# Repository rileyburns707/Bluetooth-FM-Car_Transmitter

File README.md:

# Bluetooth-FM-Car_Transmitter
This is every step I took to create a Bluetooth FM car transmitter so I could play music in my car. I started from nothing and worked through basic ideas of how it would work, the parts I would need, breadboarding it, and soldering it.

Overview:
Have a PCB that connects the BM20 chip and NS73M chip. Designed that PCB on Eagle.
Then connect M5StickC+ to PCB and program M5 using Arduino code

I will explain briefly what is needed for this project:

List of important things
- NS73M - FM transmitter
- BM20 - Bluetooth chip
- M5StickC+
- Cigarette lighter with USB-C
- PCB for NS73M for breadboard. Found one on OSH Park 
- PCB for BM20 for breadboard. Found one on OSH Park
- PCB for Bluetooth FM Transmitter. I created the PCB for this using Eagle. Everything for that PCB is in the "Eagle" file
- Arduino code. Code for the M5StickC+. Everything for that is in the "Arduino code" file
- Capacitor "EEE-FK1A560SR" from Digi-key
- Crystal "R26-32.768-12.5" from Digi-key
- Switch mode DC:DC converter "OKI-78SR-3.3/1.5-W36H-C" from Digi-key

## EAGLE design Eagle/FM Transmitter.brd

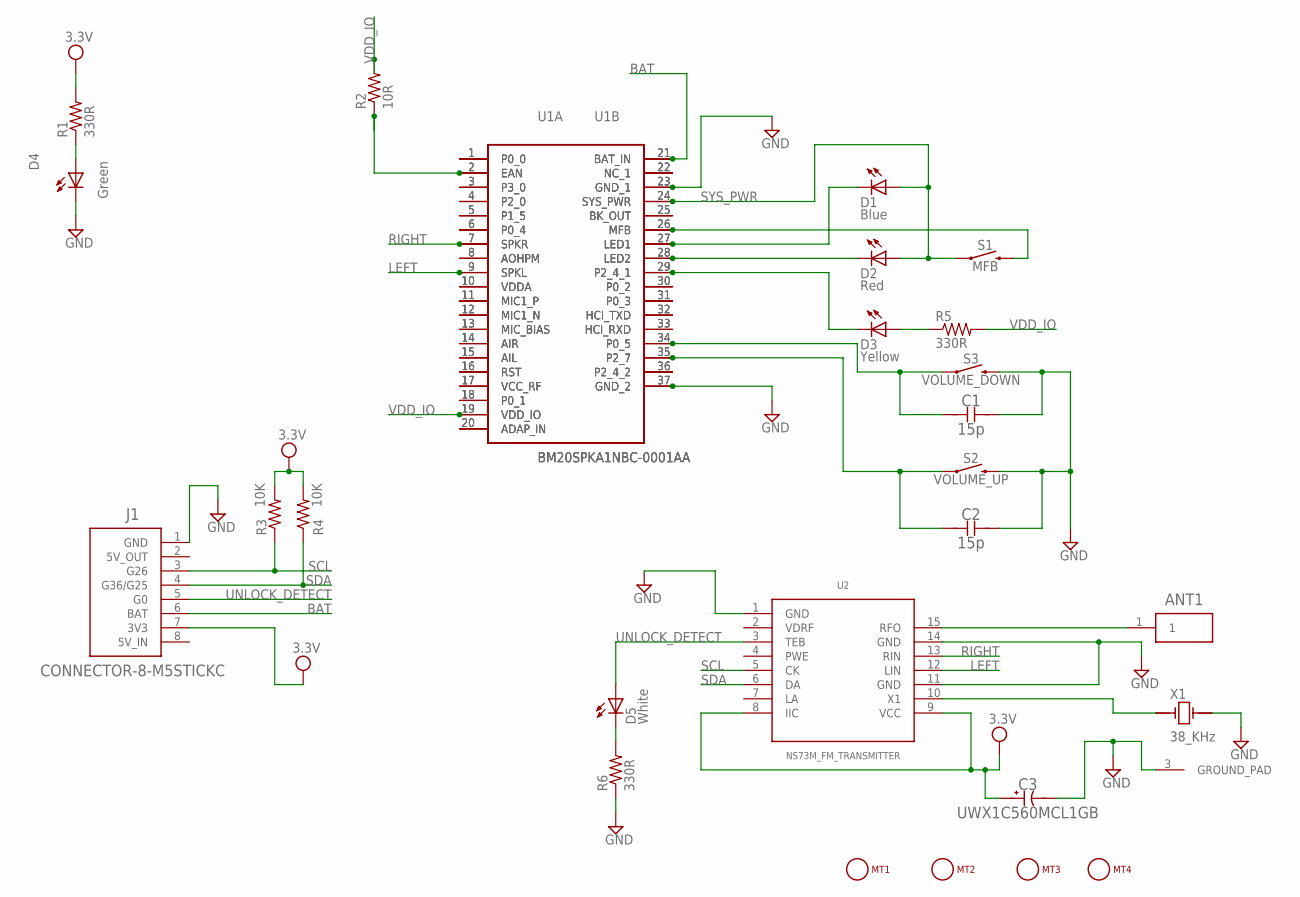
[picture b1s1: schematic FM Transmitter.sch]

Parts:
ANT1: CONNECTOR-1; ESQ-101-XX-X-S
C1, C2: 15p; CAPC2012X140N
C3: UWX1C560MCL1GB; PCAP_6.3X5.4-ELECT-M
D1: Blue; LED5MM
D2: Red; LED5MM
D3: Yellow; LED5MM
D4: Green; LED5MM
D5: White; LED5MM
J1: CONNECTOR-8-M5STICKC; ESQ-108-XX-X-S
MT1, MT2, MT3, MT4: MOUNTING_HOLE-125_250_ROUND; MT_125_250
R1, R5, R6: 330R; R0805
R2: 10R; R0805
R3, R4: 10K; R0805
S1: MFB; TACTILE_SWITCH_PTH_6.0MM
S2: VOLUME_UP; TACTILE_SWITCH_PTH_6.0MM
S3: VOLUME_DOWN; TACTILE_SWITCH_PTH_6.0MM
U1A, U1B: BM20SPKA1NBC-0001AA; BM20SPKA1NBC0001AA
U2: NS73M_FM_TRANSMITTER; NS73M
X1: 38_KHz; XTAL-WITH-GROUND-PAD

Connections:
3.3V: C3.1, J1.7 (3V3), R1.2, R3.2, R4.2, U2.8 (IIC), U2.9 (VCC)
BAT: J1.6 (BAT), U1A.21 (BAT_IN), U1B.21 (BAT_IN)
GND: C1.2, C2.2, C3.2, D4.K (C), J1.1 (GND), R6.1, S2.3 (2), S3.3 (2), U1A.23 (GND_1), U1A.37 (GND_2), U1B.23 (GND_1), U1B.37 (GND_2), U2.1 (GND), U2.11 (GND), U2.14 (GND), X1.2, X1.3 (GROUND_PAD)
LEFT: U1A.9 (SPKL), U1B.9 (SPKL), U2.12 (LIN)
unnamed: ANT1.1, U2.15 (RFO)
unnamed: D4.A, R1.1
unnamed: R2.1, U1A.2 (EAN), U1B.2 (EAN)
unnamed: D3.K (C), U1A.29 (P2_4_1), U1B.29 (P2_4_1)
unnamed: D2.K (C), U1A.28 (LED2), U1B.28 (LED2)
unnamed: D1.K (C), U1A.27 (LED1), U1B.27 (LED1)
unnamed: D3.A, R5.1
unnamed: D5.K (C), R6.2
unnamed: S1.3 (2), U1A.26 (MFB), U1B.26 (MFB)
unnamed: U2.10 (X1), X1.1
unnamed: C2.1, S2.1, U1A.35 (P2_7), U1B.35 (P2_7)
unnamed: C1.1, S3.1, U1A.34 (P0_5), U1B.34 (P0_5)
unnamed: U1A.1 (P0_0), U1B.1 (P0_0)
unnamed: U1A.3 (P3_0), U1B.3 (P3_0)
unnamed: U1A.4 (P2_0), U1B.4 (P2_0)
unnamed: U1A.5 (P1_5), U1B.5 (P1_5)
unnamed: U1A.6 (P0_4), U1B.6 (P0_4)
unnamed: U1A.8 (AOHPM), U1B.8 (AOHPM)
unnamed: U1A.10 (VDDA), U1B.10 (VDDA)
unnamed: U1A.11 (MIC1_P), U1B.11 (MIC1_P)
unnamed: U1A.12 (MIC1_N), U1B.12 (MIC1_N)
unnamed: U1A.13 (MIC_BIAS), U1B.13 (MIC_BIAS)
unnamed: U1A.14 (AIR), U1B.14 (AIR)
unnamed: U1A.15 (AIL), U1B.15 (AIL)
unnamed: U1A.16 (RST), U1B.16 (RST)
unnamed: U1A.17 (VCC_RF), U1B.17 (VCC_RF)
unnamed: U1A.18 (P0_1), U1B.18 (P0_1)
unnamed: U1A.20 (ADAP_IN), U1B.20 (ADAP_IN)
unnamed: U1A.22 (NC_1), U1B.22 (NC_1)
unnamed: U1A.25 (BK_OUT), U1B.25 (BK_OUT)
unnamed: U1A.30 (P0_2), U1B.30 (P0_2)
unnamed: U1A.31 (P0_3), U1B.31 (P0_3)
unnamed: U1A.32 (HCI_TXD), U1B.32 (HCI_TXD)
unnamed: U1A.33 (HCI_RXD), U1B.33 (HCI_RXD)
unnamed: U1A.36 (P2_4_2), U1B.36 (P2_4_2)
RIGHT: U1A.7 (SPKR), U1B.7 (SPKR), U2.13 (RIN)
SCL: J1.3 (G26), R3.1, U2.5 (CK)
SDA: J1.4 (G36/G25), R4.1, U2.6 (DA)
SYS_PWR: D1.A, D2.A, S1.1, U1A.24 (SYS_PWR), U1B.24 (SYS_PWR)
UNLOCK_DETECT: D5.A, J1.5 (G0), U2.3 (TEB)
VDD_IO: R2.2, R5.2, U1A.19 (VDD_IO), U1B.19 (VDD_IO)

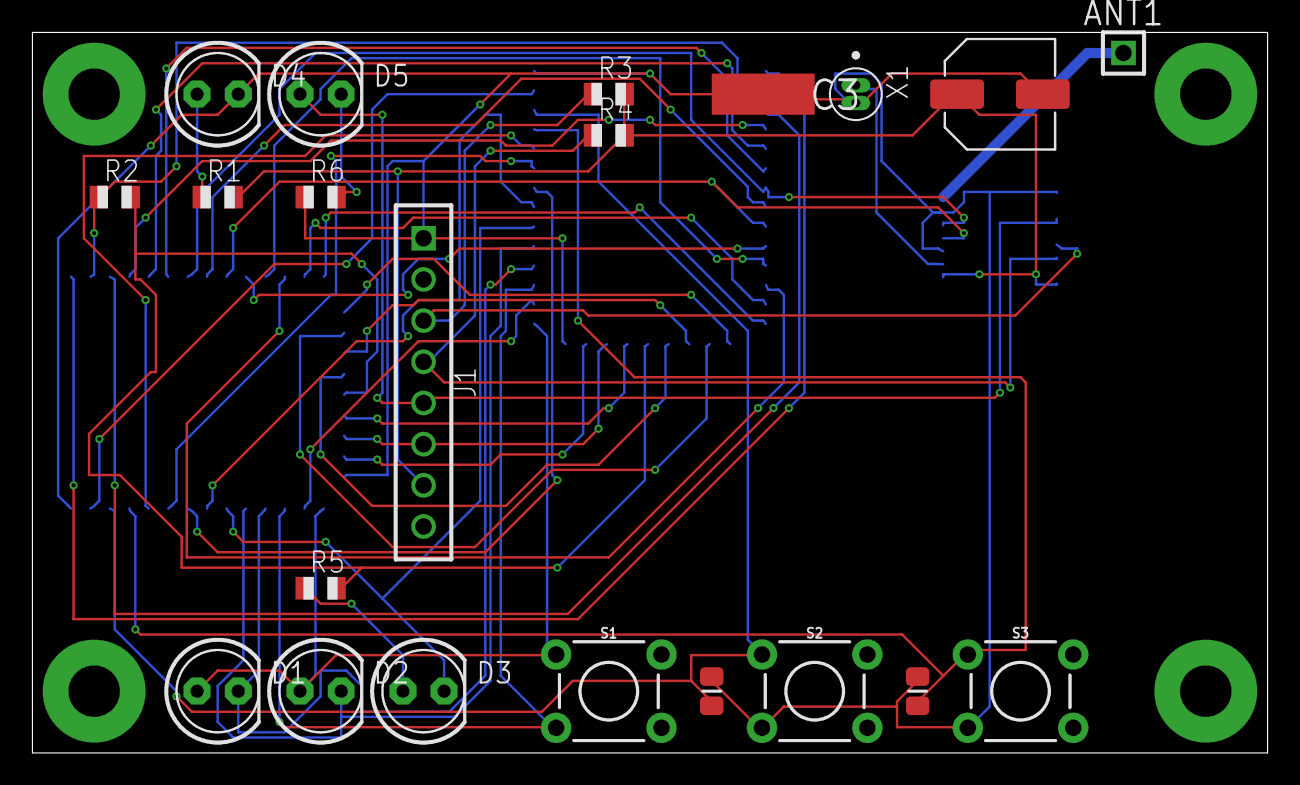
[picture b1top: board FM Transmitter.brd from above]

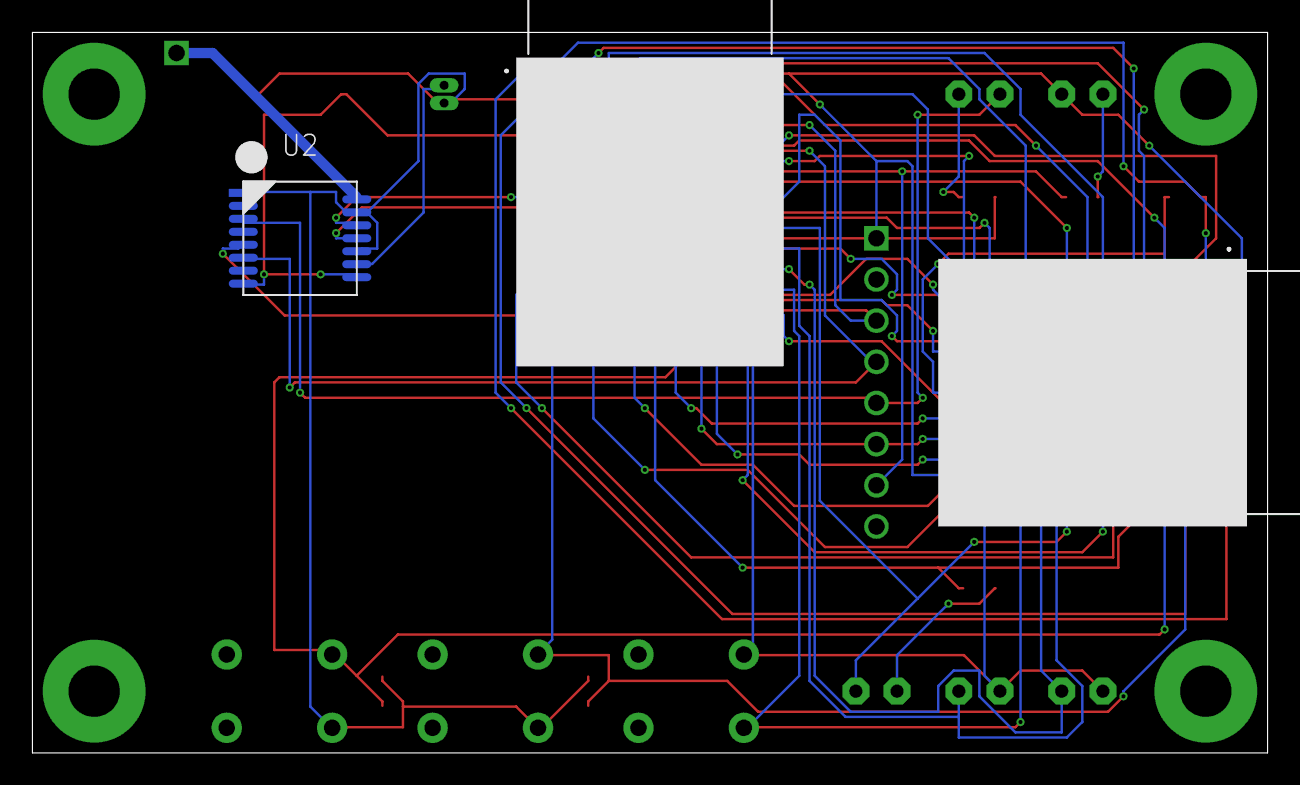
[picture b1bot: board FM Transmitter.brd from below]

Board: 2 copper layers, 76.2 x 44.5 mm, 27 parts (3 on the bottom side), 45 nets.

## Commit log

2023-09-16 Create eagle-library-BM20
2023-09-16 Eagle
2023-09-16 Update Eagle-library-BM20
2023-09-16 Create FM_Test
2023-09-16 Update FM_Test
2024-01-10 Create test
